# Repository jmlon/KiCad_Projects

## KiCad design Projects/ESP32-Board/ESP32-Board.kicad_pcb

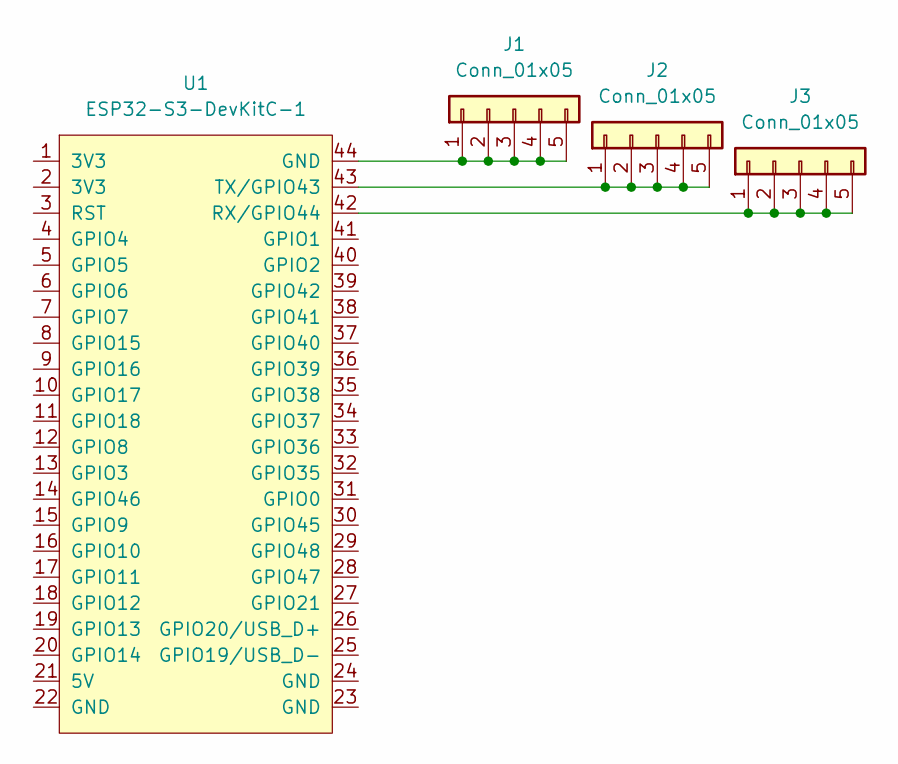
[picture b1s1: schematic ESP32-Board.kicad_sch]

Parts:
J1, J2, J3: Conn_01x05; PinHeader_1x05_P2.54mm_Vertical
U1: ESP32-S3-DevKitC-1; ESP32-S3

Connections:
unnamed: J1.1, J1.2, J1.3, J1.4, J1.5, U1.44 (GND)
unnamed: J2.1, J2.2, J2.3, J2.4, J2.5, U1.43 (TX/GPIO43)
unnamed: J3.1, J3.2, J3.3, J3.4, J3.5, U1.42 (RX/GPIO44)

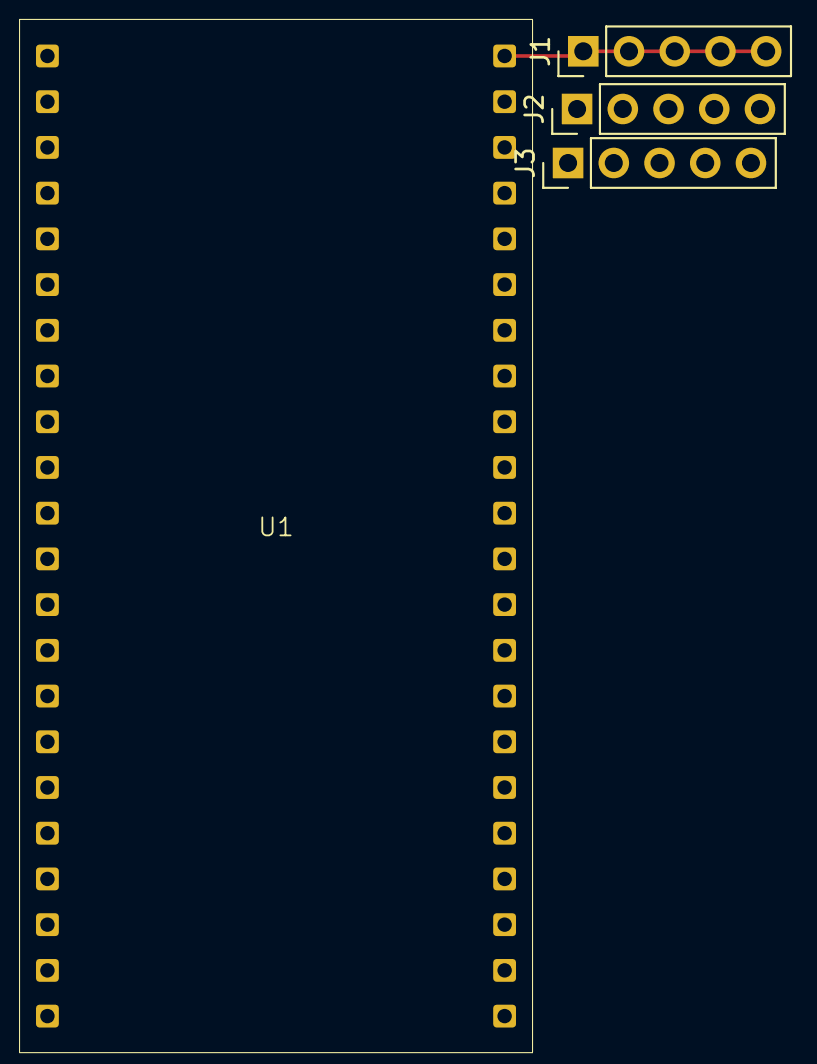
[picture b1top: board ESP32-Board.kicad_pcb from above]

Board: 2 copper layers, 4 parts (0 on the bottom side), 3 nets.

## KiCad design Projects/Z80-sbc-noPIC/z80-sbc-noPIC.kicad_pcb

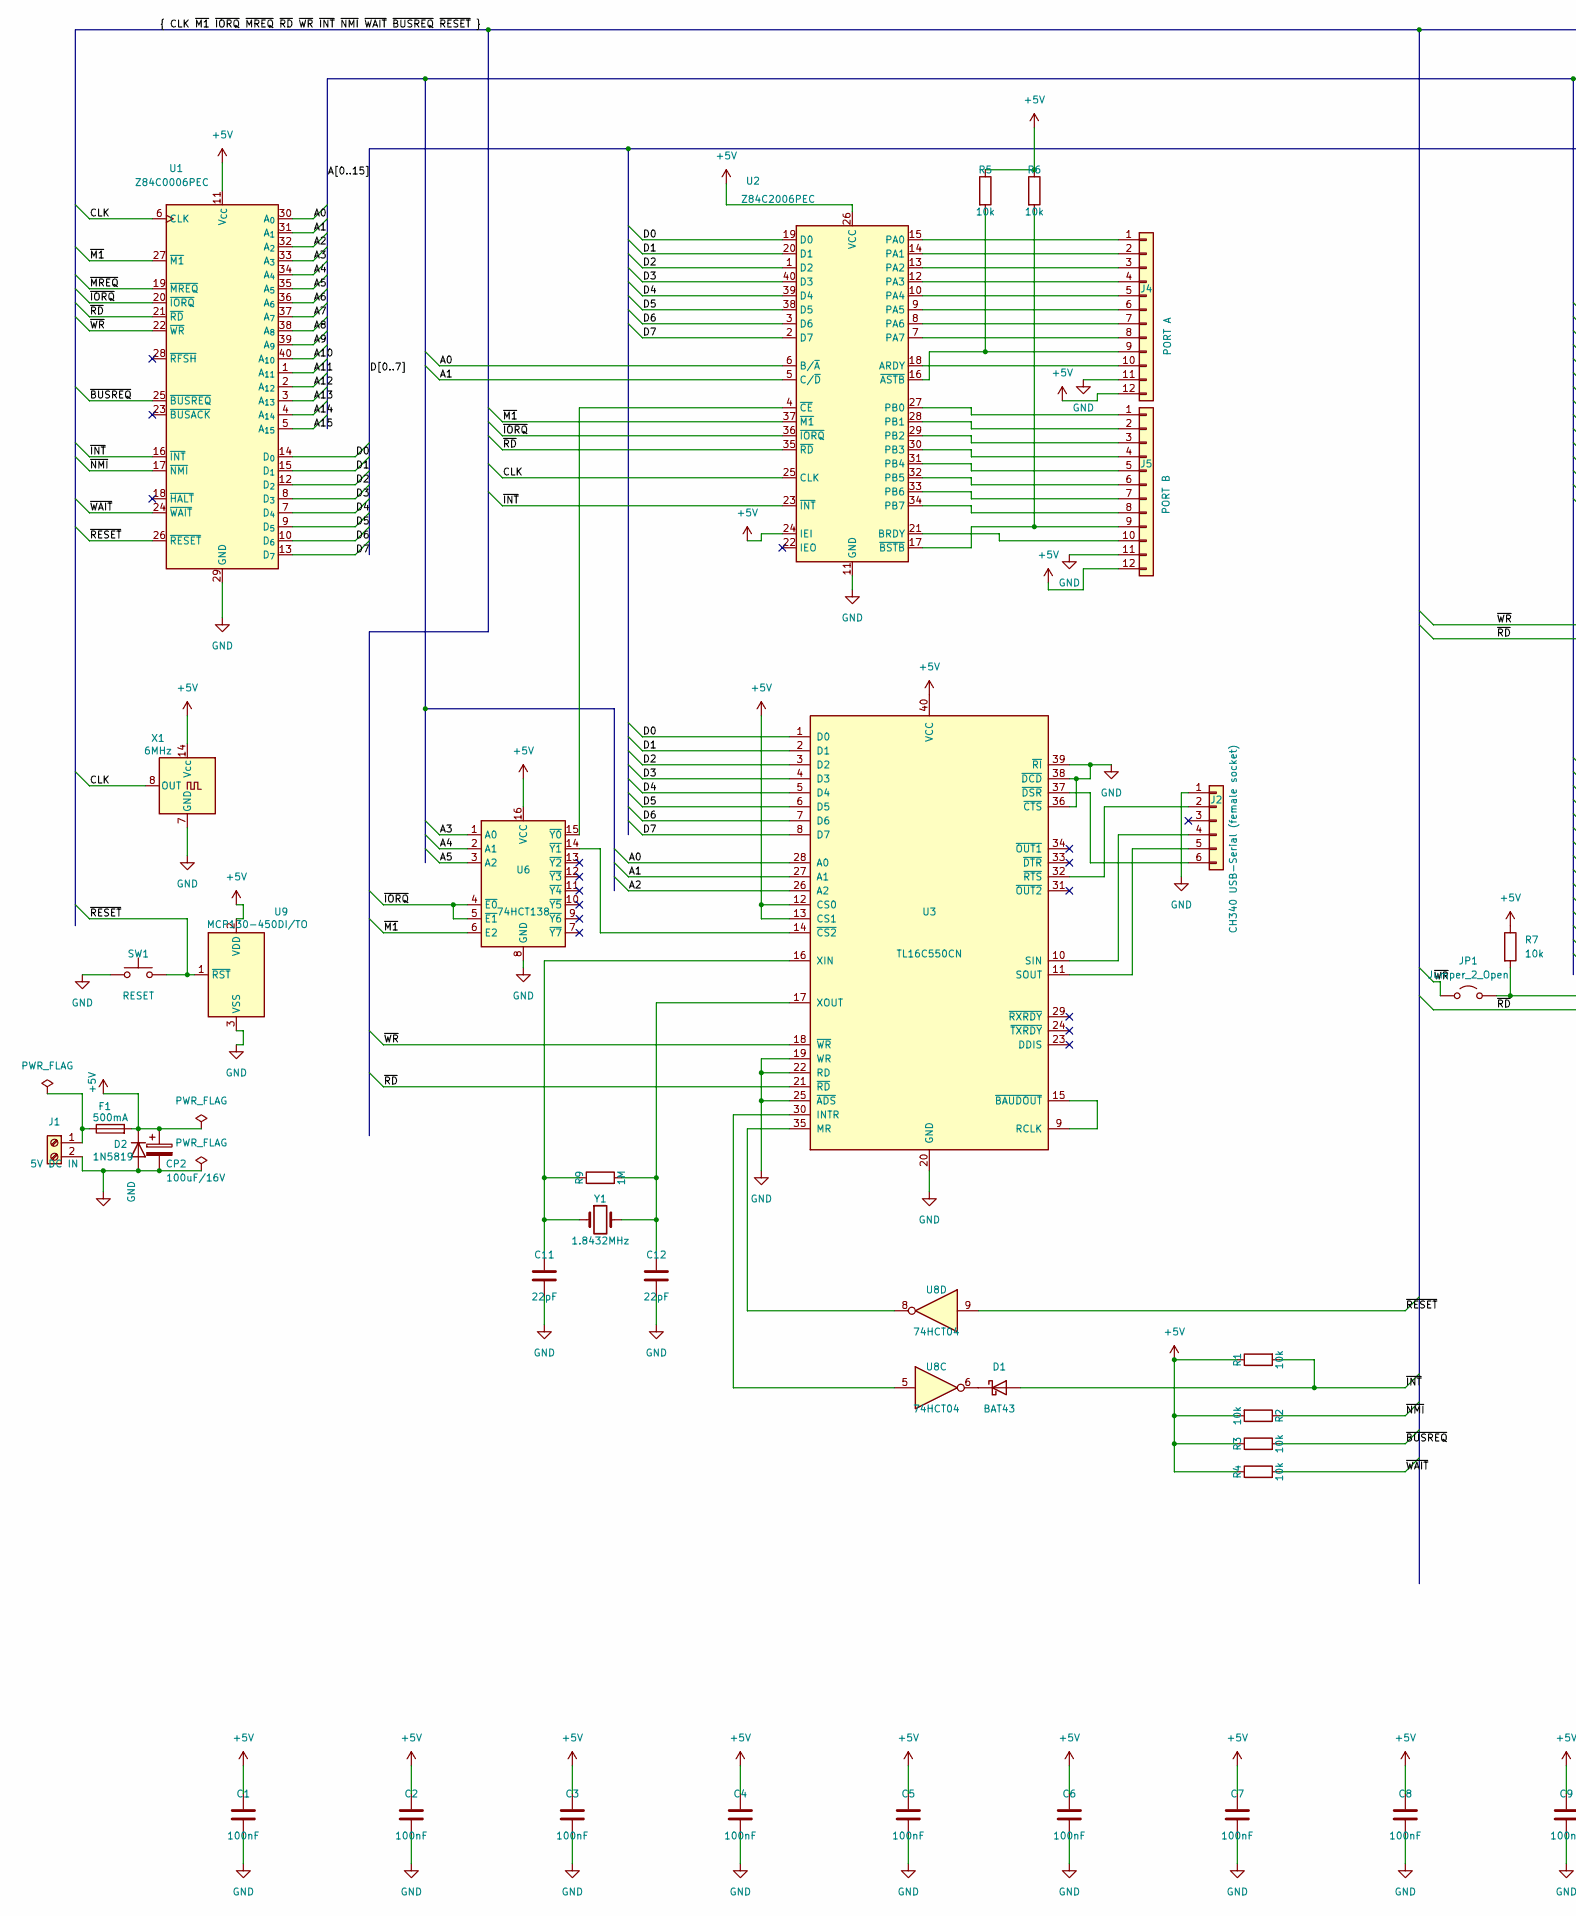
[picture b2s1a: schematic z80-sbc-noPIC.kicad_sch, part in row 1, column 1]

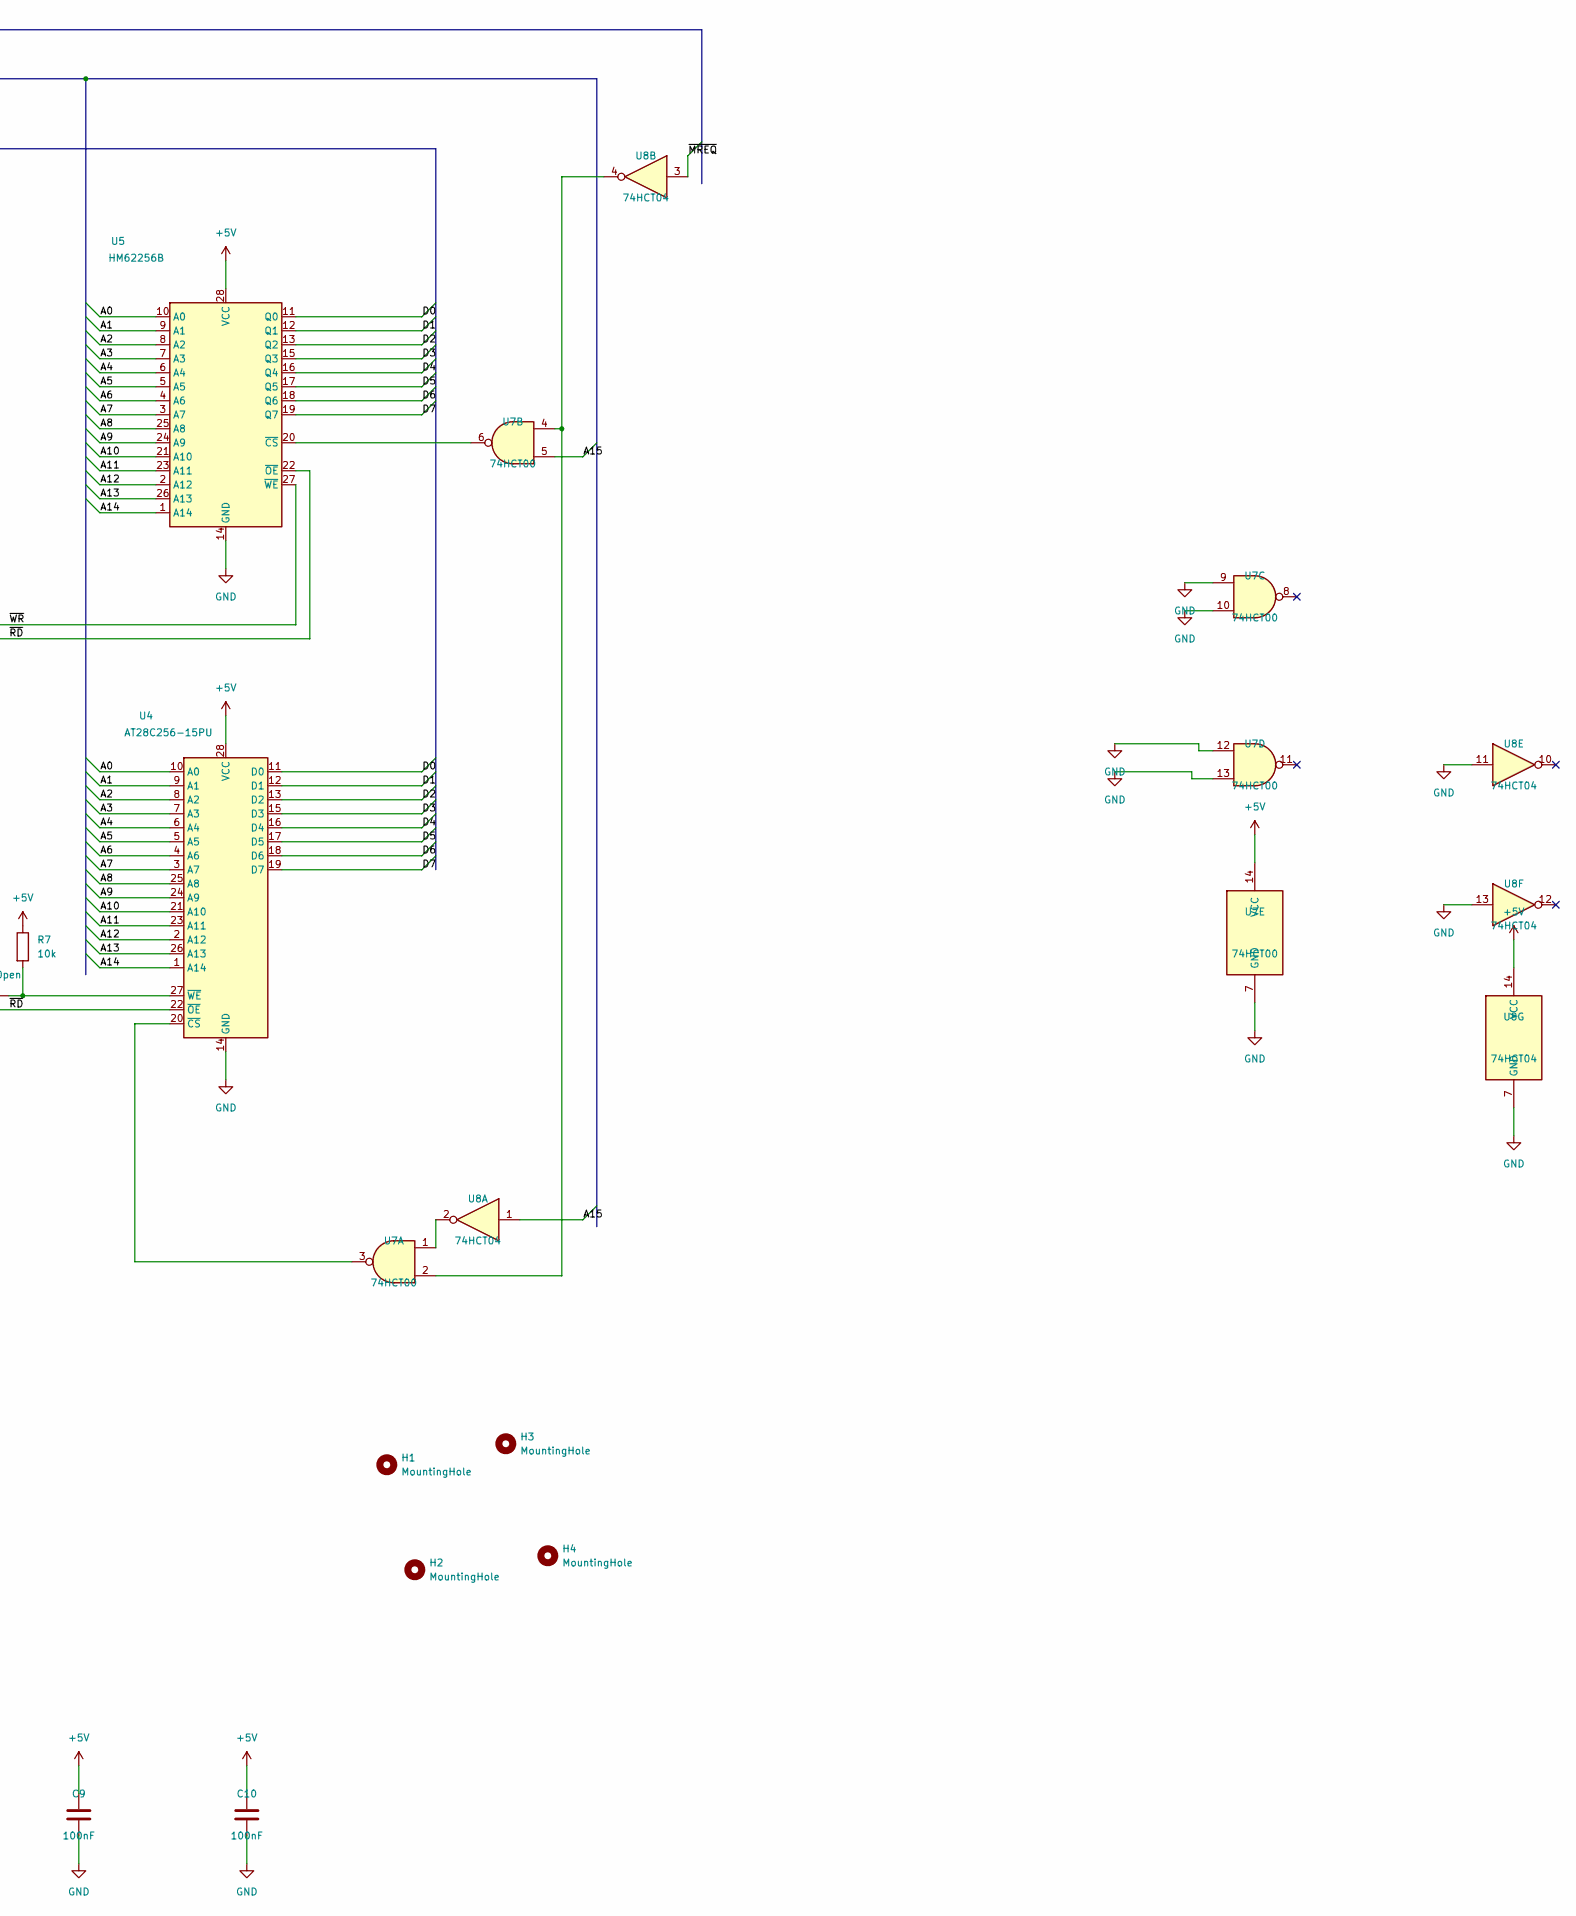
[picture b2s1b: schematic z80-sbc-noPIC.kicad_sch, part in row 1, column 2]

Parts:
C1, C2, C3, C4, C5, C6, C7, C8, C9, C10: 100nF; C_Disc_D5.0mm_W2.5mm_P5.00mm
C11, C12: 22pF; C_Disc_D5.0mm_W2.5mm_P5.00mm
CP2: 100uF/16V; CP_Radial_D6.3mm_P2.50mm
D1: BAT43; D_DO-35_SOD27_P7.62mm_Horizontal
D2: 1N5819; D_DO-41_SOD81_P10.16mm_Horizontal
F1: 500mA; RV_Disc_D7mm_W5.5mm_P5mm
H1, H2, H3, H4: MountingHole; MountingHole_3.2mm_M3
J1: 5V DC IN; TerminalBlock_Phoenix_MKDS-1,5-2-5.08_1x02_P5.08mm_Horizont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
J2: CH340 USB-Serial (female socket); PinSocket_1x06_P2.54mm_Vertical
J4: PORT A; PinHeader_1x12_P2.54mm_Vertical
J5: PORT B; PinHeader_1x12_P2.54mm_Vertical
JP1: Jumper_2_Open; PinHeader_1x02_P2.54mm_Vertical
R1, R2, R3, R4, R5, R6, R7: 10k; R_Axial_DIN0207_L6.3mm_D2.5mm_P10.16mm_Horizontal
R9: 1M; R_Axial_DIN0207_L6.3mm_D2.5mm_P10.16mm_Horizontal
SW1: RESET; SW_PUSH_6mm
U1: Z84C0006PEC; DIP-40_W15.24mm
U2: Z84C2006PEC; DIP-40_W15.24mm
U3: TL16C550CN; DIP-40_W15.24mm
U4: AT28C256-15PU; DIP-28_W15.24mm
U5: HM62256B; DIP-28_W15.24mm
U6: 74HCT138; DIP-16_W7.62mm
U7: 74HCT00; DIP-14_W7.62mm
U8: 74HCT04; DIP-14_W7.62mm
U9: MCP130-450DI/TO; TO-92_Inline_Wide
X1: 6MHz; Oscillator_DIP-14-8
Y1: 1.8432MHz; Crystal_HC49-U_Vertical

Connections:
+5V: C1.1, C2.1, C3.1, C4.1, C5.1, C6.1, C7.1, C8.1, C9.1, C10.1, CP2.1, D2.1 (K), F1.2, J4.12, J5.12, R1.1, R2.2, R3.1, R4.1, R5.1, R6.1, R7.1, U1.11 (V_{CC}), U2.24 (IEI), U2.26 (VCC), U3.12 (CS0), U3.13 (CS1), U3.40 (VCC), U4.28 (VCC), U5.28 (VCC), U6.16 (VCC), U7.14 (VCC), U8.14 (VCC), U9.2 (VDD), X1.14 (Vcc)
/A0: U1.30 (A_{0}), U2.6 (B/~A), U3.28 (A0), U4.10 (A0), U5.10 (A0)
/A1: U1.31 (A_{1}), U2.5 (C/~D), U3.27 (A1), U4.9 (A1), U5.9 (A1)
/A2: U1.32 (A_{2}), U3.26 (A2), U4.8 (A2), U5.8 (A2)
/A3: U1.33 (A_{3}), U4.7 (A3), U5.7 (A3), U6.1 (A0)
/A4: U1.34 (A_{4}), U4.6 (A4), U5.6 (A4), U6.2 (A1)
/A5: U1.35 (A_{5}), U4.5 (A5), U5.5 (A5), U6.3 (A2)
/A6: U1.36 (A_{6}), U4.4 (A6), U5.4 (A6)
/A7: U1.37 (A_{7}), U4.3 (A7), U5.3 (A7)
/A8: U1.38 (A_{8}), U4.25 (A8), U5.25 (A8)
/A9: U1.39 (A_{9}), U4.24 (A9), U5.24 (A9)
/A10: U1.40 (A_{10}), U4.21 (A10), U5.21 (A10)
/A11: U1.1 (A_{11}), U4.23 (A11), U5.23 (A11)
/A12: U1.2 (A_{12}), U4.2 (A12), U5.2 (A12)
/A13: U1.3 (A_{13}), U4.26 (A13), U5.26 (A13)
/A14: U1.4 (A_{14}), U4.1 (A14), U5.1 (A14)
/A15: U1.5 (A_{15}), U7.5, U8.1
/CLK: U1.6 (CLK), U2.25 (CLK), X1.8 (OUT)
/D0: U1.14 (D_{0}), U2.19 (D0), U3.1 (D0), U4.11 (D0), U5.11 (Q0)
/D1: U1.15 (D_{1}), U2.20 (D1), U3.2 (D1), U4.12 (D1), U5.12 (Q1)
/D2: U1.12 (D_{2}), U2.1 (D2), U3.3 (D2), U4.13 (D2), U5.13 (Q2)
/D3: U1.8 (D_{3}), U2.40 (D3), U3.4 (D3), U4.15 (D3), U5.15 (Q3)
/D4: U1.7 (D_{4}), U2.39 (D4), U3.5 (D4), U4.16 (D4), U5.16 (Q4)
/D5: U1.9 (D_{5}), U2.38 (D5), U3.6 (D5), U4.17 (D5), U5.17 (Q5)
/D6: U1.10 (D_{6}), U2.3 (D6), U3.7 (D6), U4.18 (D6), U5.18 (Q6)
/D7: U1.13 (D_{7}), U2.2 (D7), U3.8 (D7), U4.19 (D7), U5.19 (Q7)
/~BUSREQ: R3.2, U1.25 (~BUSREQ)
/~INT: D1.2 (A), R1.2, U1.16 (~INT), U2.23 (~INT)
/~IORQ: U1.20 (~IORQ), U2.36 (~IORQ), U6.4 (~E0), U6.5 (~E1)
/~M1: U1.27 (~M1), U2.37 (~M1), U6.6 (E2)
/~MREQ: U1.19 (~MREQ), U8.3
/~NMI: R2.1, U1.17 (~NMI)
/~RD: U1.21 (~RD), U2.35 (~RD), U3.21 (~RD), U4.22 (~OE), U5.22 (~OE)
/~RESET: SW1.1, U1.26 (~RESET), U8.9, U9.1 (~RST)
/~WAIT: R4.2, U1.24 (~WAIT)
/~WR: JP1.1 (A), U1.22 (~WR), U3.18 (~WR), U5.27 (~WE)
GND: C1.2, C2.2, C3.2, C4.2, C5.2, C6.2, C7.2, C8.2, C9.2, C10.2, C11.2, C12.2, CP2.2, D2.2 (A), J1.2, J2.1, J4.11, J5.11, SW1.2, U1.29 (GND), U2.11 (GND), U3.19 (WR), U3.20 (GND), U3.22 (RD), U3.25 (~ADS), U3.36 (~CTS), U3.38 (~DCD), U3.39 (~RI), U4.14 (GND), U5.14 (GND), U6.8 (GND), U7.7 (GND), U7.9, U7.10, U7.12, U7.13, U8.7 (GND), U8.11, U8.13, U9.3 (VSS), X1.7 (GND)
unnamed: D1.1 (K), U8.6
unnamed: F1.1, J1.1
unnamed: J2.2, U3.32 (~RTS)
unnamed: J2.4, U3.10 (SIN)
unnamed: J2.5, U3.11 (SOUT)
unnamed: J2.6, U3.37 (~DSR)
unnamed: J4.1, U2.15 (PA0)
unnamed: J4.2, U2.14 (PA1)
unnamed: J4.3, U2.13 (PA2)
unnamed: J4.4, U2.12 (PA3)
unnamed: J4.5, U2.10 (PA4)
unnamed: J4.6, U2.9 (PA5)
unnamed: J4.7, U2.8 (PA6)
unnamed: J4.8, U2.7 (PA7)
unnamed: J4.9, R5.2, U2.16 (~ASTB)
unnamed: J4.10, U2.18 (ARDY)
unnamed: J5.1, U2.27 (PB0)
unnamed: J5.2, U2.28 (PB1)
unnamed: J5.3, U2.29 (PB2)
unnamed: J5.4, U2.30 (PB3)
unnamed: J5.5, U2.31 (PB4)
unnamed: J5.6, U2.32 (PB5)
unnamed: J5.7, U2.33 (PB6)
unnamed: J5.8, U2.34 (PB7)
unnamed: J5.9, R6.2, U2.17 (~BSTB)
unnamed: J5.10, U2.21 (BRDY)
unnamed: JP1.2 (B), R7.2, U4.27 (~WE)
unnamed: U2.4 (~CE), U6.15 (~Y0)
unnamed: U3.30 (INTR), U8.5
unnamed: U3.35 (MR), U8.8
unnamed: U3.9 (RCLK), U3.15 (~BAUDOUT)
unnamed: C11.1, R9.1, U3.16 (XIN), Y1.1
unnamed: C12.1, R9.2, U3.17 (XOUT), Y1.2
unnamed: U3.14 (~CS2), U6.14 (~Y1)
unnamed: U4.20 (~CS), U7.3
unnamed: U5.20 (~CS), U7.6
unnamed: U7.1, U8.2
unnamed: U7.2, U7.4, U8.4

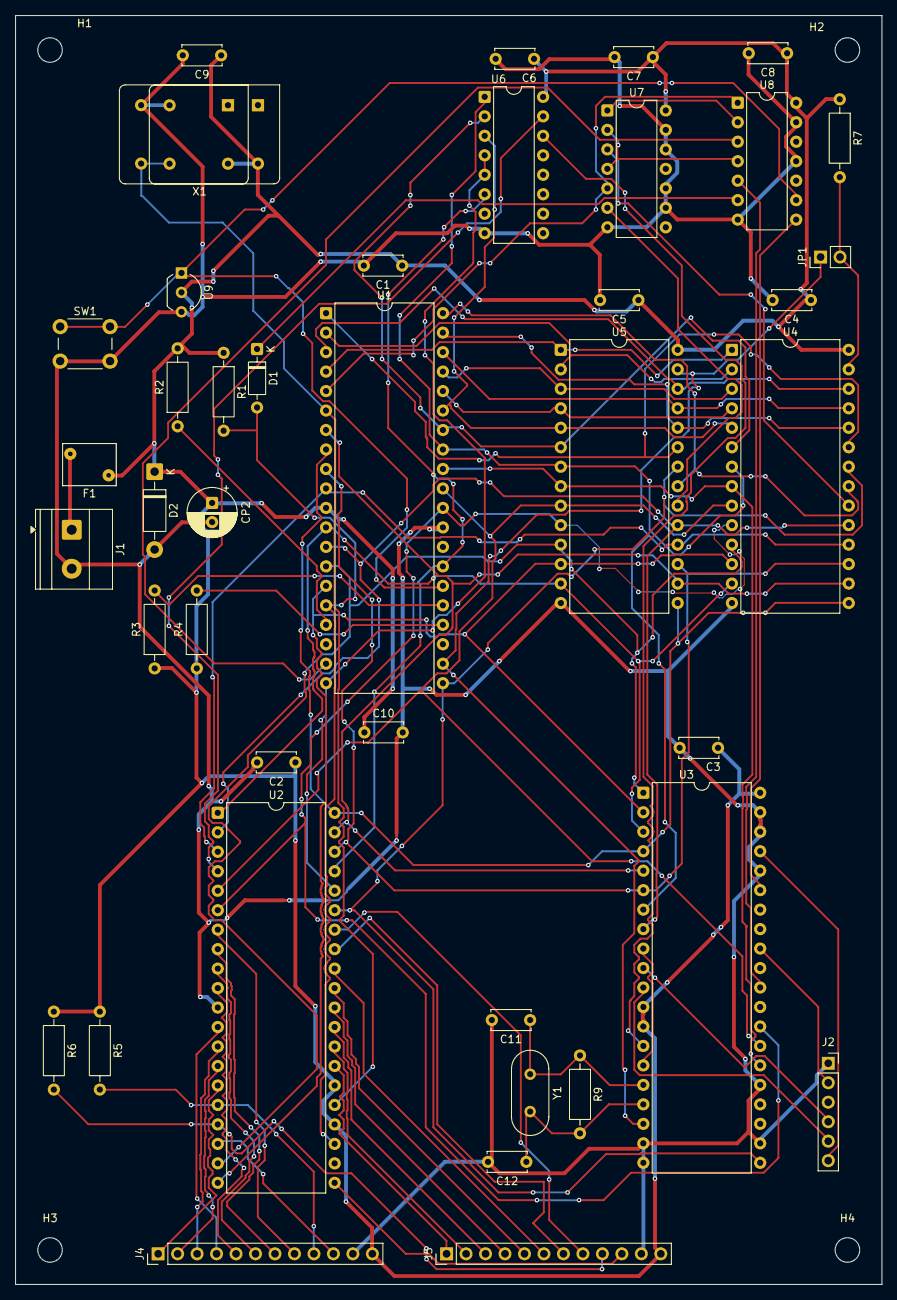
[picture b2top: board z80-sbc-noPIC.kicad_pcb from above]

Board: 2 copper layers, 113.0 x 165.5 mm, 45 parts (0 on the bottom side), 75 nets.
